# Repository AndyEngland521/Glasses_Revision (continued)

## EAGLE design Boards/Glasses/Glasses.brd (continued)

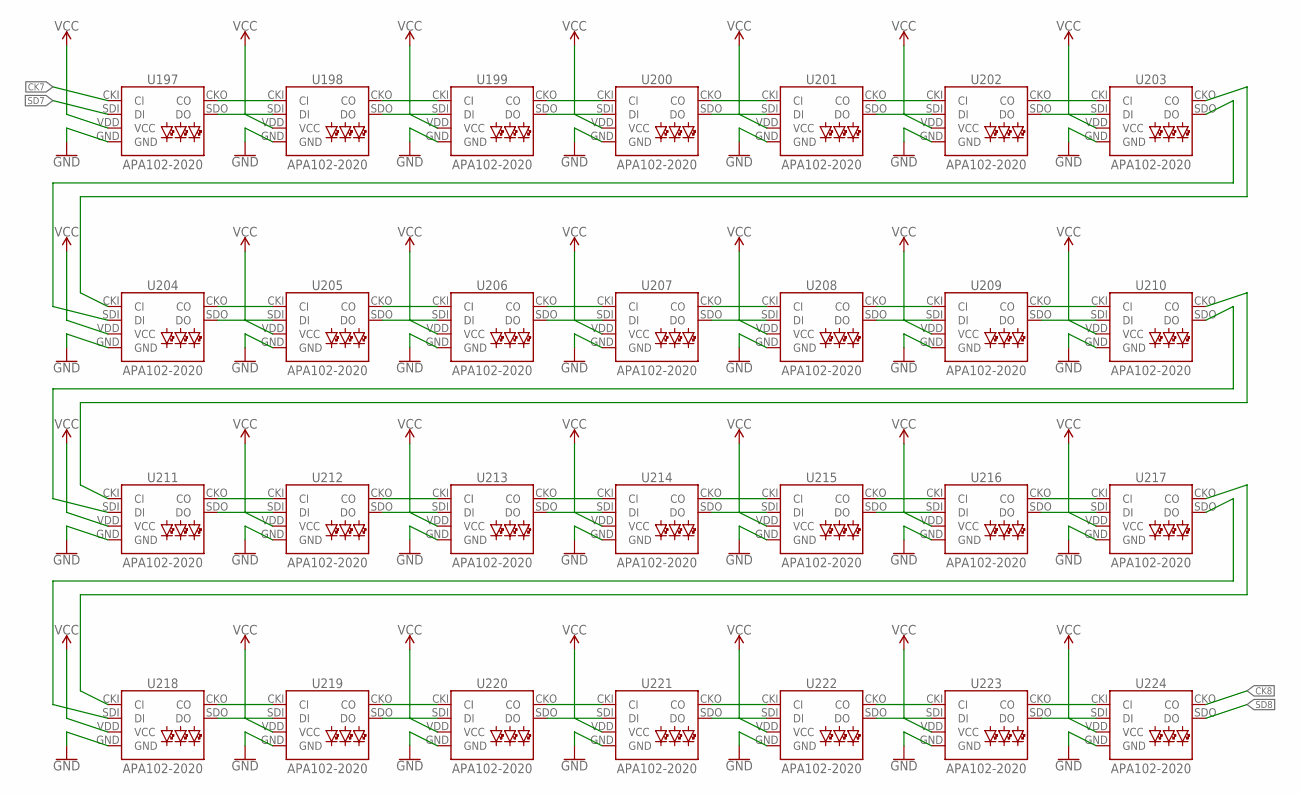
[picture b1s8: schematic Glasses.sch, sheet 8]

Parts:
U197, U198, U199, U200, U201, U202, U203, U204, U205, U206, U207, U208, U209, U210, U211, U212, U213, U214, U215, U216, U217, U218, U219, U220, U221, U222, U223, U224: APA102-2020

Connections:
CK7: U197.CKI (CI); also elsewhere on the board
CK8: U224.CKO (CO); also elsewhere on the board
GND: U197.GND, U198.GND, U199.GND, U200.GND, U201.GND, U202.GND, U203.GND, U204.GND, U205.GND, U206.GND, U207.GND, U208.GND, U209.GND, U210.GND, U211.GND, U212.GND, U213.GND, U214.GND, U215.GND, U216.GND, U217.GND, U218.GND, U219.GND, U220.GND, U221.GND, U222.GND, U223.GND, U224.GND; also elsewhere on the board
unnamed: U197.SDO (DO), U198.SDI (DI)
unnamed: U197.CKO (CO), U198.CKI (CI)
unnamed: U198.CKO (CO), U199.CKI (CI)
unnamed: U198.SDO (DO), U199.SDI (DI)
unnamed: U199.SDO (DO), U200.SDI (DI)
unnamed: U199.CKO (CO), U200.CKI (CI)
unnamed: U200.CKO (CO), U201.CKI (CI)
unnamed: U200.SDO (DO), U201.SDI (DI)
unnamed: U201.CKO (CO), U202.CKI (CI)
unnamed: U201.SDO (DO), U202.SDI (DI)
unnamed: U202.CKO (CO), U203.CKI (CI)
unnamed: U202.SDO (DO), U203.SDI (DI)
unnamed: U204.SDO (DO), U205.SDI (DI)
unnamed: U204.CKO (CO), U205.CKI (CI)
unnamed: U205.CKO (CO), U206.CKI (CI)
unnamed: U205.SDO (DO), U206.SDI (DI)
unnamed: U206.SDO (DO), U207.SDI (DI)
unnamed: U206.CKO (CO), U207.CKI (CI)
unnamed: U207.CKO (CO), U208.CKI (CI)
unnamed: U207.SDO (DO), U208.SDI (DI)
unnamed: U208.CKO (CO), U209.CKI (CI)
unnamed: U208.SDO (DO), U209.SDI (DI)
unnamed: U209.CKO (CO), U210.CKI (CI)
unnamed: U209.SDO (DO), U210.SDI (DI)
unnamed: U203.SDO (DO), U204.SDI (DI)
unnamed: U203.CKO (CO), U204.CKI (CI)
unnamed: U211.SDO (DO), U212.SDI (DI)
unnamed: U211.CKO (CO), U212.CKI (CI)
unnamed: U212.CKO (CO), U213.CKI (CI)
unnamed: U212.SDO (DO), U213.SDI (DI)
unnamed: U213.SDO (DO), U214.SDI (DI)
unnamed: U213.CKO (CO), U214.CKI (CI)
unnamed: U214.CKO (CO), U215.CKI (CI)
unnamed: U214.SDO (DO), U215.SDI (DI)
unnamed: U215.CKO (CO), U216.CKI (CI)
unnamed: U215.SDO (DO), U216.SDI (DI)
unnamed: U216.CKO (CO), U217.CKI (CI)
unnamed: U216.SDO (DO), U217.SDI (DI)
unnamed: U217.SDO (DO), U218.SDI (DI)
unnamed: U217.CKO (CO), U218.CKI (CI)
unnamed: U210.SDO (DO), U211.SDI (DI)
unnamed: U210.CKO (CO), U211.CKI (CI)
unnamed: U218.CKO (CO), U219.CKI (CI)
unnamed: U218.SDO (DO), U219.SDI (DI)
unnamed: U219.CKO (CO), U220.CKI (CI)
unnamed: U219.SDO (DO), U220.SDI (DI)
unnamed: U220.SDO (DO), U221.SDI (DI)
unnamed: U220.CKO (CO), U221.CKI (CI)
unnamed: U221.CKO (CO), U222.CKI (CI)
unnamed: U221.SDO (DO), U222.SDI (DI)
unnamed: U222.CKO (CO), U223.CKI (CI)
unnamed: U222.SDO (DO), U223.SDI (DI)
unnamed: U223.CKO (CO), U224.CKI (CI)
unnamed: U223.SDO (DO), U224.SDI (DI)
SD7: U197.SDI (DI); also elsewhere on the board
SD8: U224.SDO (DO); also elsewhere on the board
VCC: U197.VDD (VCC), U198.VDD (VCC), U199.VDD (VCC), U200.VDD (VCC), U201.VDD (VCC), U202.VDD (VCC), U203.VDD (VCC), U204.VDD (VCC), U205.VDD (VCC), U206.VDD (VCC), U207.VDD (VCC), U208.VDD (VCC), U209.VDD (VCC), U210.VDD (VCC), U211.VDD (VCC), U212.VDD (VCC), U213.VDD (VCC), U214.VDD (VCC), U215.VDD (VCC), U216.VDD (VCC), U217.VDD (VCC), U218.VDD (VCC), U219.VDD (VCC), U220.VDD (VCC), U221.VDD (VCC), U222.VDD (VCC), U223.VDD (VCC), U224.VDD (VCC); also elsewhere on the board

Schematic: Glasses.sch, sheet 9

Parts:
U225, U226, U227, U228, U229, U230, U231, U232, U233, U234, U235, U236, U237, U238, U239, U240, U241, U242, U243, U244, U245, U246, U247, U248, U249, U250, U251, U252: APA102-2020

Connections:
CK8: U225.CKI (CI); also elsewhere on the board
GND: U225.GND, U226.GND, U227.GND, U228.GND, U229.GND, U230.GND, U231.GND, U232.GND, U233.GND, U234.GND, U235.GND, U236.GND, U237.GND, U238.GND, U239.GND, U240.GND, U241.GND, U242.GND, U243.GND, U244.GND, U245.GND, U246.GND, U247.GND, U248.GND, U249.GND, U250.GND, U251.GND, U252.GND; also elsewhere on the board
unnamed: U225.SDO (DO), U226.SDI (DI)
unnamed: U225.CKO (CO), U226.CKI (CI)
unnamed: U226.CKO (CO), U227.CKI (CI)
unnamed: U226.SDO (DO), U227.SDI (DI)
unnamed: U227.SDO (DO), U228.SDI (DI)
unnamed: U227.CKO (CO), U228.CKI (CI)
unnamed: U228.CKO (CO), U229.CKI (CI)
unnamed: U228.SDO (DO), U229.SDI (DI)
unnamed: U229.CKO (CO), U230.CKI (CI)
unnamed: U229.SDO (DO), U230.SDI (DI)
unnamed: U230.CKO (CO), U231.CKI (CI)
unnamed: U230.SDO (DO), U231.SDI (DI)
unnamed: U232.SDO (DO), U233.SDI (DI)
unnamed: U232.CKO (CO), U233.CKI (CI)
unnamed: U233.CKO (CO), U234.CKI (CI)
unnamed: U233.SDO (DO), U234.SDI (DI)
unnamed: U234.SDO (DO), U235.SDI (DI)
unnamed: U234.CKO (CO), U235.CKI (CI)
unnamed: U235.CKO (CO), U236.CKI (CI)
unnamed: U235.SDO (DO), U236.SDI (DI)
unnamed: U236.CKO (CO), U237.CKI (CI)
unnamed: U236.SDO (DO), U237.SDI (DI)
unnamed: U237.CKO (CO), U238.CKI (CI)
unnamed: U237.SDO (DO), U238.SDI (DI)
unnamed: U231.SDO (DO), U232.SDI (DI)
unnamed: U231.CKO (CO), U232.CKI (CI)
unnamed: U239.SDO (DO), U240.SDI (DI)
unnamed: U239.CKO (CO), U240.CKI (CI)
unnamed: U240.CKO (CO), U241.CKI (CI)
unnamed: U240.SDO (DO), U241.SDI (DI)
unnamed: U241.SDO (DO), U242.SDI (DI)
unnamed: U241.CKO (CO), U242.CKI (CI)
unnamed: U242.CKO (CO), U243.CKI (CI)
unnamed: U242.SDO (DO), U243.SDI (DI)
unnamed: U243.CKO (CO), U244.CKI (CI)
unnamed: U243.SDO (DO), U244.SDI (DI)
unnamed: U244.CKO (CO), U245.CKI (CI)
unnamed: U244.SDO (DO), U245.SDI (DI)
unnamed: U245.SDO (DO), U246.SDI (DI)
unnamed: U245.CKO (CO), U246.CKI (CI)
unnamed: U238.SDO (DO), U239.SDI (DI)
unnamed: U238.CKO (CO), U239.CKI (CI)
unnamed: U246.CKO (CO), U247.CKI (CI)
unnamed: U246.SDO (DO), U247.SDI (DI)
unnamed: U247.CKO (CO), U248.CKI (CI)
unnamed: U247.SDO (DO), U248.SDI (DI)
unnamed: U248.SDO (DO), U249.SDI (DI)
unnamed: U248.CKO (CO), U249.CKI (CI)
unnamed: U249.CKO (CO), U250.CKI (CI)
unnamed: U249.SDO (DO), U250.SDI (DI)
unnamed: U250.CKO (CO), U251.CKI (CI)
unnamed: U250.SDO (DO), U251.SDI (DI)
unnamed: U251.CKO (CO), U252.CKI (CI)
unnamed: U251.SDO (DO), U252.SDI (DI)
SD8: U225.SDI (DI); also elsewhere on the board
VCC: U225.VDD (VCC), U226.VDD (VCC), U227.VDD (VCC), U228.VDD (VCC), U229.VDD (VCC), U230.VDD (VCC), U231.VDD (VCC), U232.VDD (VCC), U233.VDD (VCC), U234.VDD (VCC), U235.VDD (VCC), U236.VDD (VCC), U237.VDD (VCC), U238.VDD (VCC), U239.VDD (VCC), U240.VDD (VCC), U241.VDD (VCC), U242.VDD (VCC), U243.VDD (VCC), U244.VDD (VCC), U245.VDD (VCC), U246.VDD (VCC), U247.VDD (VCC), U248.VDD (VCC), U249.VDD (VCC), U250.VDD (VCC), U251.VDD (VCC), U252.VDD (VCC); also elsewhere on the board

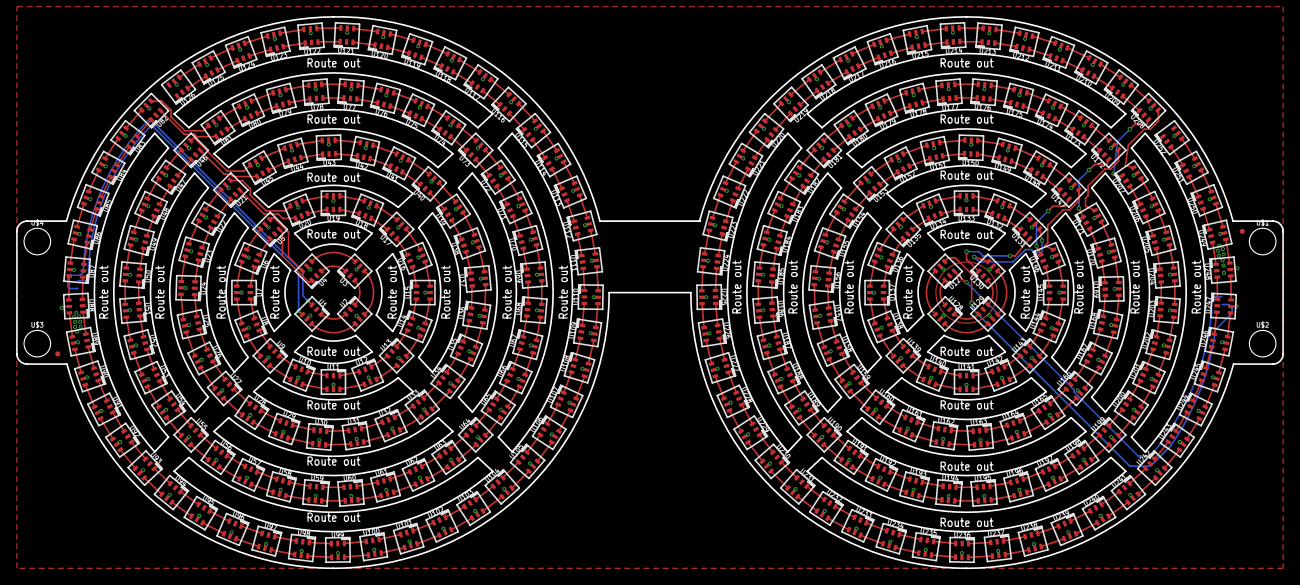
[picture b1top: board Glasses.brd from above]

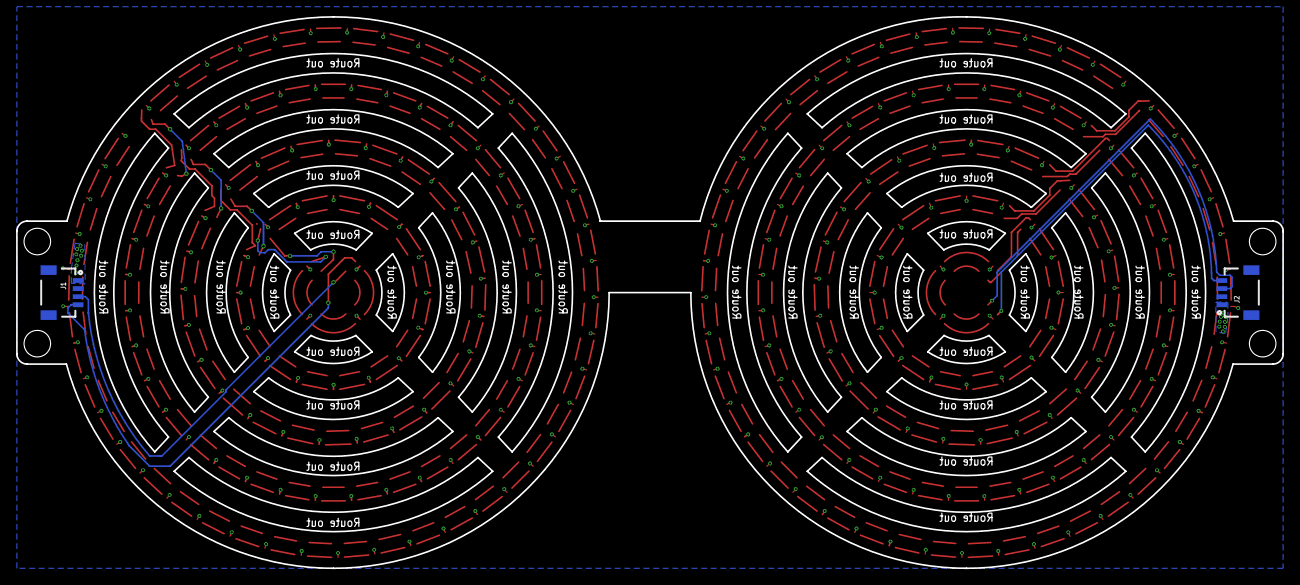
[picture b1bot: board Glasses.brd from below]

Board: 2 copper layers, 157.5 x 68.6 mm, 260 parts (2 on the bottom side), 506 nets.

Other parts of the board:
U$1, U$2, U$3, U$4: STAND-OFF

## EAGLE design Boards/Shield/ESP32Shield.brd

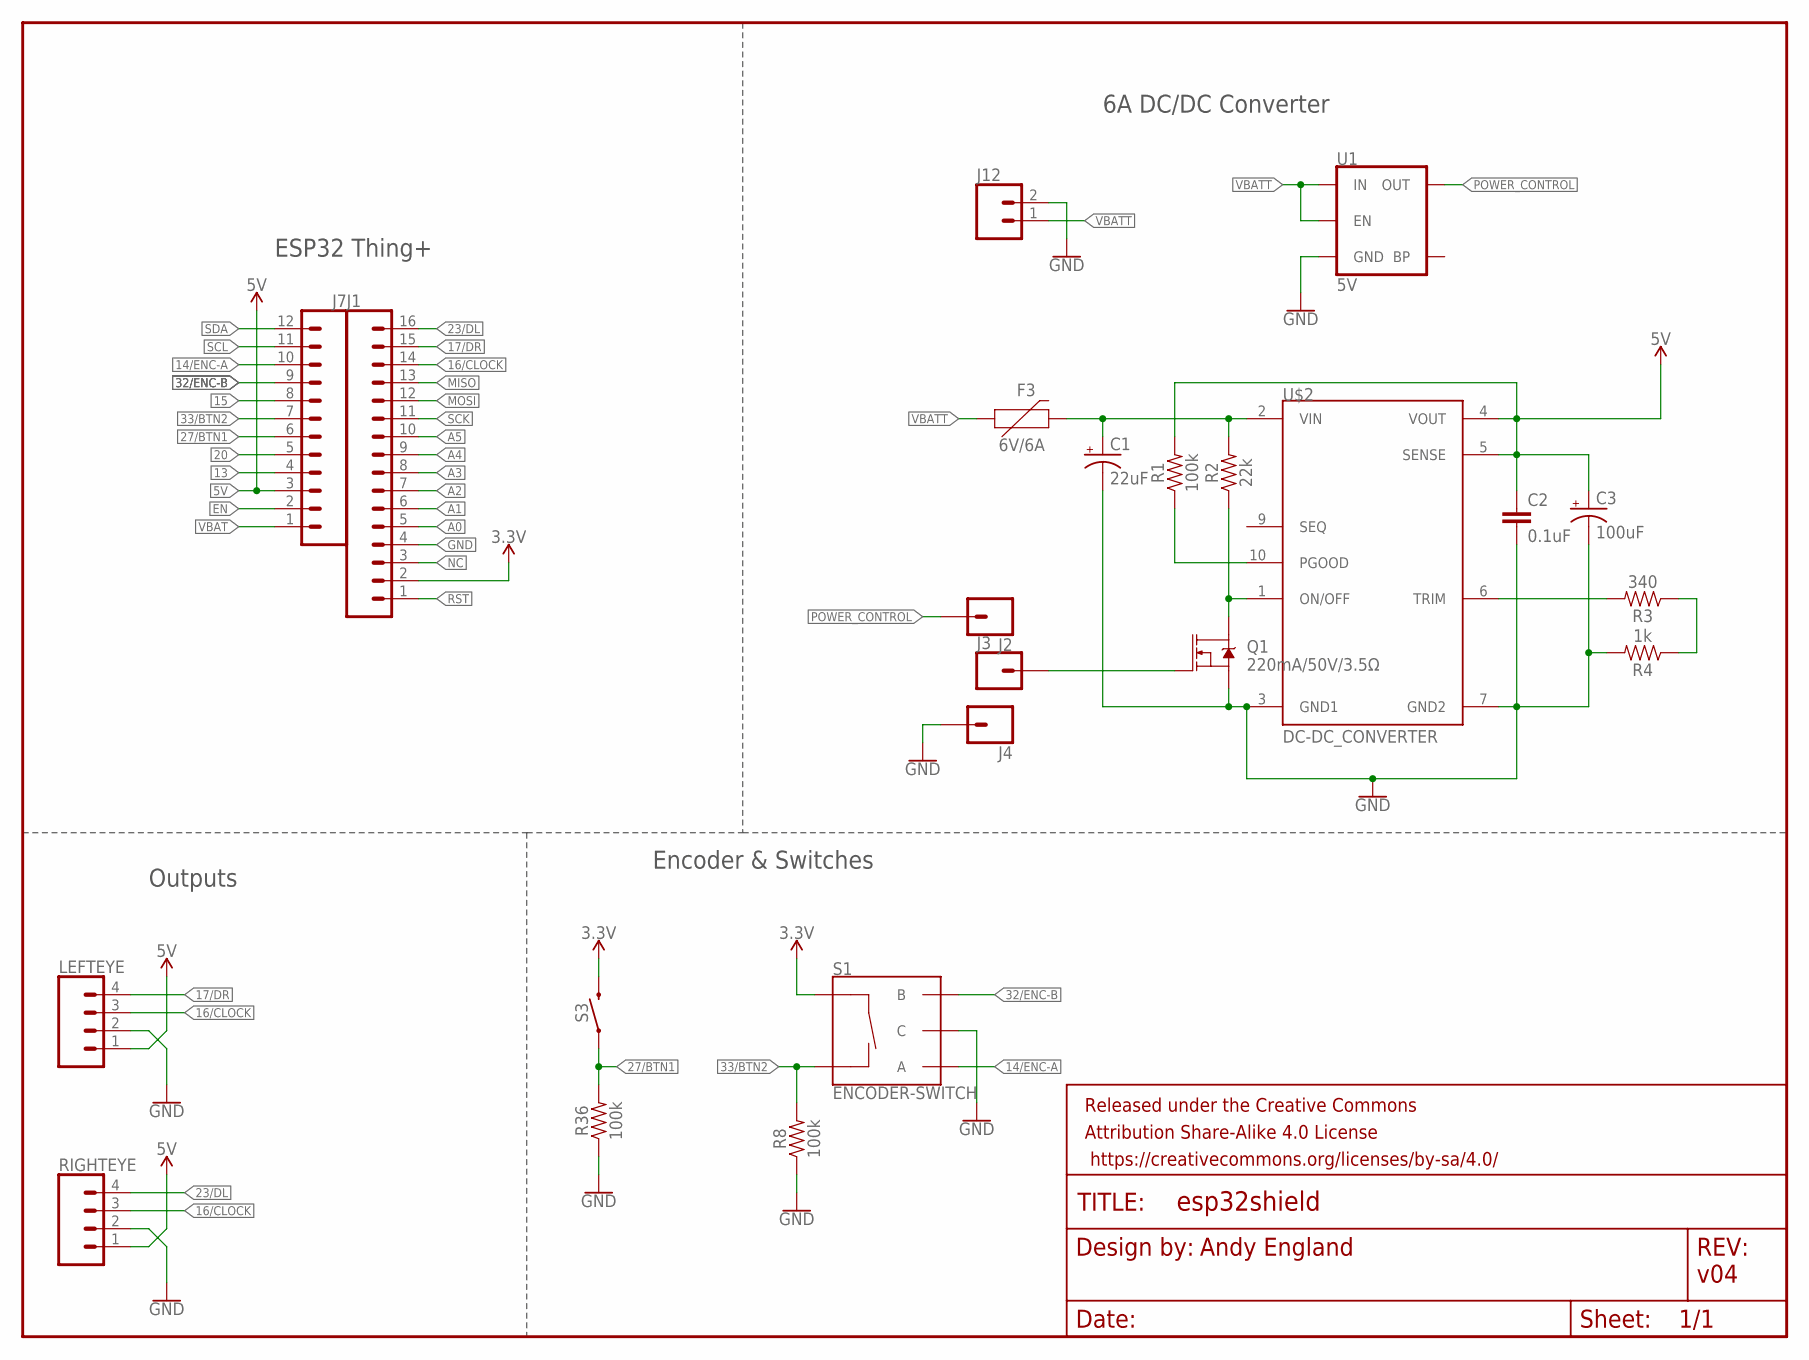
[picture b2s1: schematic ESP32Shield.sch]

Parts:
C1: 22uF; PANASONIC_C
C2: 0.1uF; 0603
C3: 100uF; PANASONIC_D
F3: 6V/6A; 1206
FRAME1: FRAME-LETTER; CREATIVE_COMMONS
J1: CONN_161X16_NO_SILK; 1X16_NO_SILK
J2, J3, J4: CONN_01; 1X01
J7: CONN_12NO_SILK; 1X12_NO_SILK
J12: CONN_025MM; SCREWTERMINAL-5MM-2
LEFTEYE: CONN_041X04_NO_SILK; 1X04_NO_SILK
Q1: 220mA/50V/3.5Ω; SOT23-3
R1, R8, R36: 100k; 0603
R2: 22k; 0603
R3: 340; 0603
R4: 1k; 0603
RIGHTEYE: CONN_041X04_NO_SILK; 1X04_NO_SILK
S1: ENCODER-SWITCH; ROTARY_ENC_PLAIN
S3: MOMENTARY-SWITCH-SPST-SMD-5.2-REDUNDANT; TACTILE_SWITCH_SMD_5.2MM
U1: 5V; SOT23-5
U$2: DC-DC_CONVERTER

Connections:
3.3V: J1.2, S1.SW+, S3.3 (2), S3.4 (2)
5V: C2.1, C3.+, J7.3, LEFTEYE.1, R1.2, RIGHTEYE.1, U$2.4 (VOUT), U$2.5 (SENSE)
13: J7.4
14/ENC-A: J7.10, S1.A
15: J7.8
16/CLOCK: J1.14, LEFTEYE.3, RIGHTEYE.3
17/DR: J1.15, LEFTEYE.4
20: J7.5
23/DL: J1.16, RIGHTEYE.4
27/BTN1: J7.6, R36.2, S3.1, S3.2 (1)
32/ENC-B: J7.9, S1.B
33/BTN2: J7.7, R8.2, S1.SW-
A0: J1.5
A1: J1.6
A2: J1.7
A3: J1.8
A4: J1.9
A5: J1.10
EN: J7.2
GND: C1.-, C2.2, C3.-, J1.4, J4.1, J12.2, LEFTEYE.2, Q1.2 (S), R4.2, R8.1, R36.1, RIGHTEYE.2, S1.C, U1.2 (GND), U$2.3 (GND1), U$2.7 (GND2)
MISO: J1.13
MOSI: J1.12
unnamed: J3.1, Q1.1 (G)
unnamed: C1.+, F3.2, R2.2, U$2.2 (VIN)
unnamed: Q1.3 (D), R2.1, U$2.1 (ON/OFF)
unnamed: R3.2, U$2.6 (TRIM)
unnamed: R3.1, R4.1
NC: J1.3
PGOOD3: R1.1, U$2.10 (PGOOD)
POWER_CONTROL: J2.1, U1.5 (OUT)
RST: J1.1
SCK: J1.11
SCL: J7.11
SDA: J7.12
VBAT: J7.1
VBATT: F3.1, J12.1, U1.1 (IN), U1.3 (EN)

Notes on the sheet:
ESP32 Thing+
6A DC/DC Converter
Encoder & Switches
Outputs
Andy England
v04

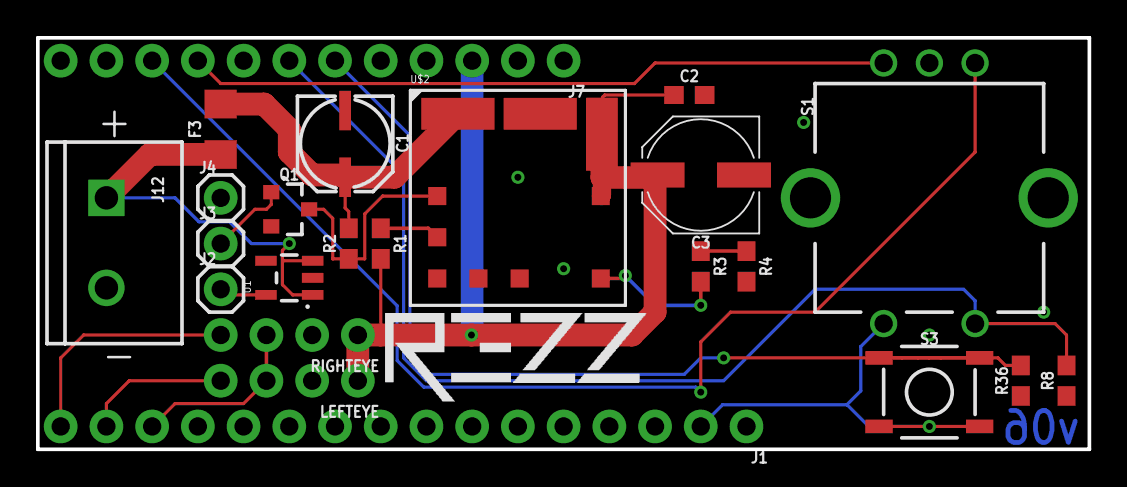
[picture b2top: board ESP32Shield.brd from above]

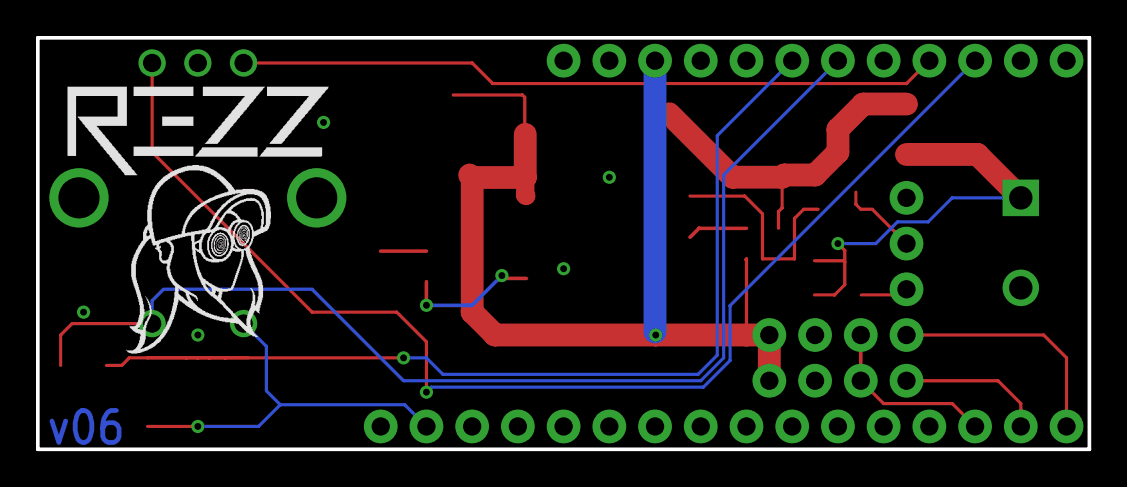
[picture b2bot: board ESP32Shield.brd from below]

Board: 2 copper layers, 58.4 x 22.9 mm, 27 parts (2 on the bottom side), 18 nets.

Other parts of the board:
U$1, U$4: SWBADNC#JPG
U$3: FB847930393B0F397FC054233C2D7CC6F23D0E39#JPG

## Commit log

2017-11-10 initial commit, board design
2017-11-13 began laying out glasses shape
2017-11-13 added .brd files
2017-11-13 added mockup printout
2017-11-13 Post-print changes
2017-11-14 laid out LED's
2017-12-01 changed diameter, began LED layout
2017-12-02 laid out footpirnts, routing needed
2017-12-04 Laid out most of board
2017-12-05 ordered v01
2017-12-13 Added stems
2017-12-13 glasses brd
2017-12-13 Added stem .gcode
2017-12-20 stem v02
2017-12-20 added stemv02.gcode
2017-12-21 Stem v03
2017-12-21 added .gcode
2017-12-22 added other side of stem
2017-12-22 Stem v04
2017-12-22 added stem.gcode
2018-03-06 started artnet eyeball
2018-03-06 adding singleLED
2018-03-07 added resolume project
2018-03-07 organized directory
2018-03-08 cleaned ARTNET code
2018-03-09 cleaning code still
2018-03-15 updating tutorial images
2018-03-15 added artnet demo
2018-03-15 updated advanced output picture
2018-03-23 updated code
2018-03-23 added presets
2018-03-26 Added stem options
2018-03-26 added .gcode for stems
2018-03-28 updated demo
2018-03-30 added stems d and e
2018-03-30 added de gcode
2018-04-09 beginning ESP32 Shield schematic
2018-04-10 Laid out ESP32 Shield
2018-04-11 began layout
2018-04-12 finished ESP32 Shield layout
2018-04-23 added brainbucket
2018-04-23 updating measures on board
2018-04-25 added gcode
2018-04-26 adding new pushbutton
2018-05-03 Added braincap
2018-05-03 added cap, made so batteries fit
2018-05-14 updated resistors, silk
2018-06-01 adding menus
2018-06-04 menu work
2018-06-05 updating code
2018-06-06 more menu changes
2018-06-07 added SSID and password editing
2018-06-07 adding to editchar func
2018-06-12 up to date menus
2018-06-12 Updating interrupts, power structure
2018-06-13 updating board
2018-06-14 adding new ESP8266Thing shield gerber
2018-06-14 adding Eyemap
2018-06-15 adding a possible map
2018-06-15 updating housing
2018-06-15 adding map, angle functions
2018-06-16 map almost finished, need to get offsets
2018-06-19 adding splashscreen
2018-06-20 finished map, added gradspin to menu
2018-06-20 Adding button and knob
2018-06-20 Adding gcode for knob and button
2018-06-22 Updating stem and button
2018-06-22 adding gcode for stem and button
2018-06-22 updating knob and button
2018-06-23 add knob button
2018-06-23 Updating knob to multipart assembly
2018-06-23 updating knoob gcode
2018-06-23 updating knob
2018-06-23 updating to new gcode
2018-09-14 pushing stl
2018-09-14 adding brainbucket
2018-09-17 updating brainbucket
2018-09-17 adding new brainbucket
2018-09-18 fixing interrupt capabilities
2018-09-20 updated brainbucket
2018-09-20 updating gcode
2018-09-20 Updating to ESP32 WROOM
2018-09-28 updating shield
2018-10-10 updating board to V06, finangling code to work with WROOM
2018-10-11 changing menus to enums, organizing code, fixed screen
2018-10-26 adding new patterns
2018-11-07 changing patterns to struct
2018-12-05 adding stem .stl
    have battery powered device. adding stems to glasses.
2018-12-05 adding final case
    adding final case, both with and without belt loop
2018-12-05 adding brainbucketnoloop
2018-12-05 Updating to new button
2018-12-05 Adding slot for qwiic
2018-12-06 adding gcode
2019-09-18 gcode for button
